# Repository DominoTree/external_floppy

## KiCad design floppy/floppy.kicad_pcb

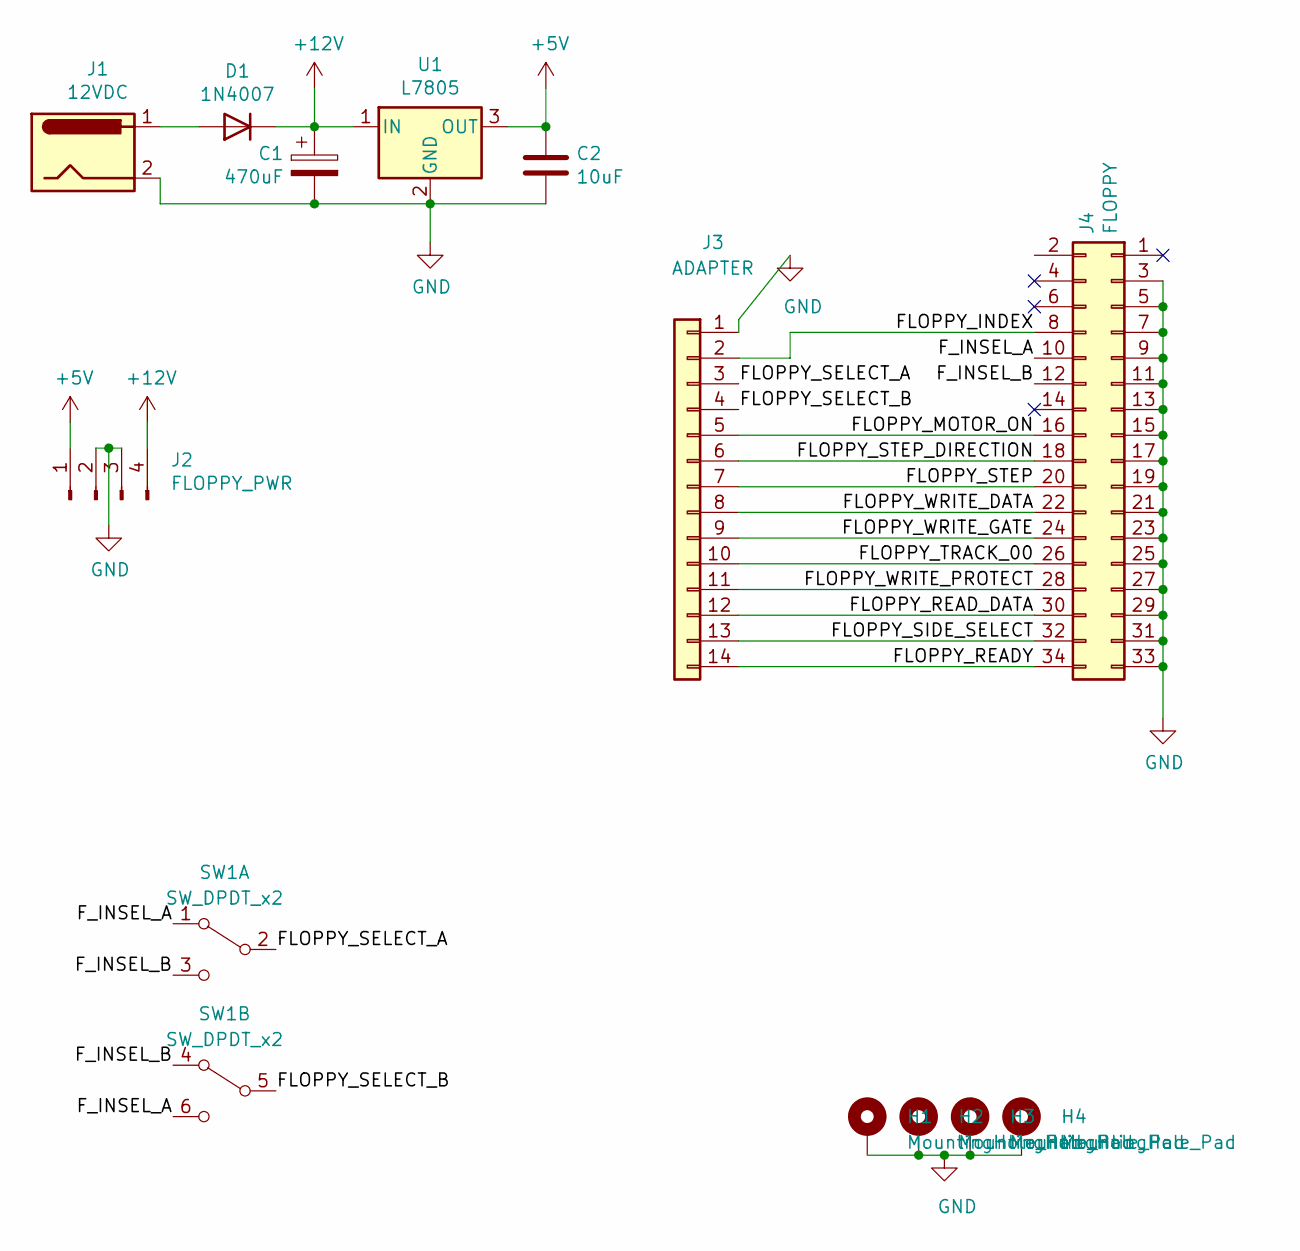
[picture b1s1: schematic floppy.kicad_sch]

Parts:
C1: 470uF; C_Radial_D10.0mm_H12.5mm_P5.00mm
C2: 10uF; C_Disc_D10.0mm_W2.5mm_P5.00mm
D1: 1N4007; D_DO-41_SOD81_P7.62mm_Horizontal
H1, H2, H3, H4: MountingHole_Pad; MountingHole_3.2mm_M3_DIN965_Pad_TopBottom
J1: 12VDC; BarrelJack_Horizontal
J2: FLOPPY_PWR; Molex_KK-254_AE-6410-04A_1x04_P2.54mm_Vertical
J3: ADAPTER; IDC-Header_2x07_P2.54mm_Horizontal
J4: FLOPPY; IDC-Header_2x17_P2.54mm_Vertical
SW1: SW_DPDT_x2; SW_CuK_JS202011AQN_DPDT_Angled
U1: L7805; TO-220-3_Horizontal_TabDown

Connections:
+5V: C2.1, J2.1, U1.3 (OUT)
+12V: C1.1, D1.1 (K), J2.4, U1.1 (IN)
/FLOPPY_INDEX: J3.2, J4.8
/FLOPPY_MOTOR_ON: J3.5, J4.16
/FLOPPY_READY: J3.14, J4.34
/FLOPPY_READ_DATA: J3.12, J4.30
/FLOPPY_SELECT_A: J3.3, SW1.2 (B)
/FLOPPY_SELECT_B: J3.4, SW1.5 (B)
/FLOPPY_SIDE_SELECT: J3.13, J4.32
/FLOPPY_STEP: J3.7, J4.20
/FLOPPY_STEP_DIRECTION: J3.6, J4.18
/FLOPPY_TRACK_00: J3.10, J4.26
/FLOPPY_WRITE_DATA: J3.8, J4.22
/FLOPPY_WRITE_GATE: J3.9, J4.24
/FLOPPY_WRITE_PROTECT: J3.11, J4.28
/F_INSEL_A: J4.10, SW1.1 (A), SW1.6 (C)
/F_INSEL_B: J4.12, SW1.3 (C), SW1.4 (A)
GND: C1.2, C2.2, H1.1, H2.1, H3.1, H4.1, J1.2, J2.2, J2.3, J3.1, J4.3, J4.5, J4.7, J4.9, J4.11, J4.13, J4.15, J4.17, J4.19, J4.21, J4.23, J4.25, J4.27, J4.29, J4.31, J4.33, U1.2 (GND)
unnamed: D1.2 (A), J1.1

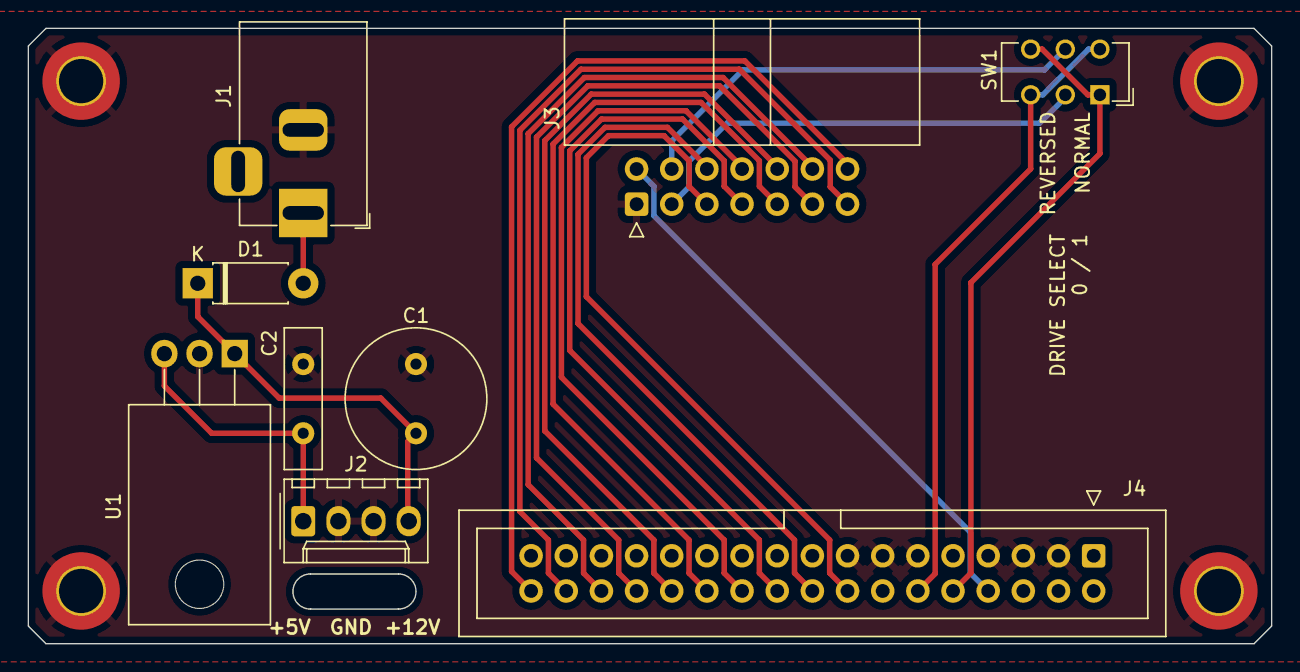
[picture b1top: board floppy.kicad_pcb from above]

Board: 2 copper layers, 89.8 x 44.5 mm, 13 parts (0 on the bottom side), 19 nets.

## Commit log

2021-01-16 there was shrinkage
2021-02-15 break up boards
